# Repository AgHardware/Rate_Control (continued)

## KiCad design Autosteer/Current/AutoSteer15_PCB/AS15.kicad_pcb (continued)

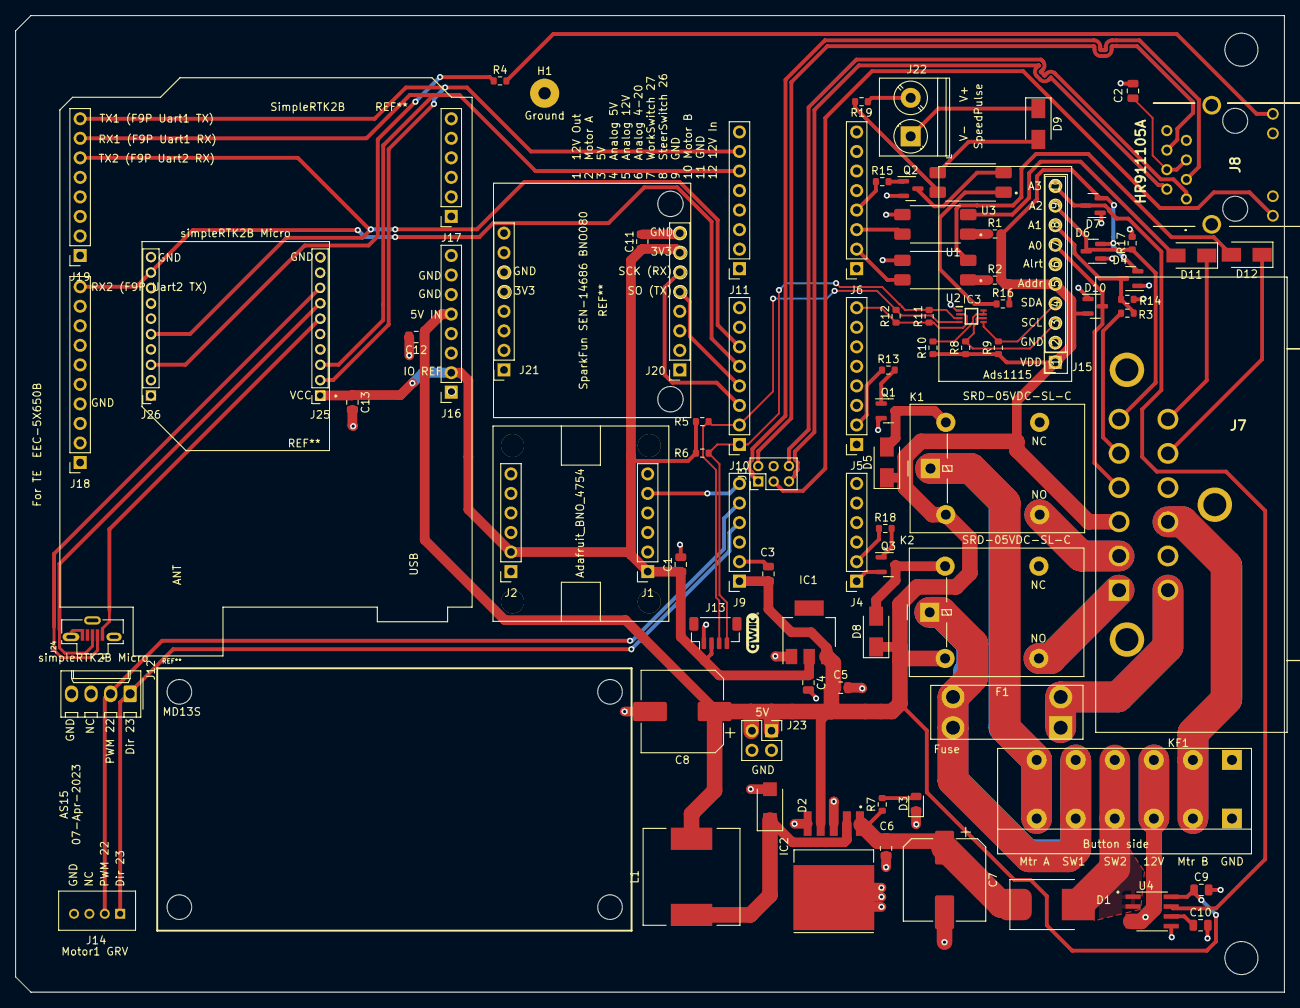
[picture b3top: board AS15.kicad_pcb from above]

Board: 2 copper layers, 165.0 x 127.0 mm, 88 parts (0 on the bottom side), 68 nets.

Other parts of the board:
 : M4; MountingHole_4.3mm_M4
 #2: M4; MountingHole_4.3mm_M4

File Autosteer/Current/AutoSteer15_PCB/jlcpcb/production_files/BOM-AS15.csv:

Comment,Designator,Footprint,LCSC
ACS712ELCTR30AT,U4,SOIC127P600X175-8N,C10681
250,R17,R_0603_1608Metric,C114613
SS36,D2,SMA(DO-214AC),C116712
HR911105A,J8,HR911105A,C12074
150,R4,R_0603_1608Metric,C126805
I2C-3V3,J13,Qwic_vertical,C145961
10uF,C5,C_0805_2012Metric,C15850
S10MC,D1,D_SMC_larger_pads,C169472
1K,"R13,R15,R18,R7",R_0603_1608Metric,C21190
217,"R11,R12",R_0603_1608Metric,C22953
470,"R1,R16,R19,R2",R_0603_1608Metric,C23179
BAV99,"D10,D4,D6,D7",SOT-23,C2500
200K,R10,R_0603_1608Metric,C25811
Conn_01x08_Female,"J10,J11,J16,J19,J20,J21,J5,J6",PinSocket_1x08_P2.54mm_Vertical,C27438
5K,R3,R_0603_1608Metric,C2828621
1uF,C6,C_0805_2012Metric,C28323
ADS1115 - 1001001,"J15,J18",PinSocket_1x10_P2.54mm_Vertical,C2897373
C2935469,F1,Fuse_Holder_C2935469,C2935469
PCA9306DCUR,IC3,PCA9306DCUR,C33196
341,"R8,R9",R_0603_1608Metric,C334802
470uF,C7,CP_Elec_10x10.5,C3350
Conn_01x10_Female,"J25,J26",PinSocket_1x10_P2.00mm_Vertical,C350282
SRD-05VDC-SL-C,"K1,K2",Songle_SRD-05VDC-SL-C,C35449
Motor1 GRV,J14,Grove,C403774
Conn_01x06_Female,"J1,J17,J2,J4,J9",PinSocket_1x06_P2.54mm_Vertical,C40877
2.2K,"R5,R6",R_0603_1608Metric,C4190
3K,R14,R_0603_1608Metric,C4211
SpeedPulse,J22,"TerminalBlock_Phoenix_PT-1,5-2-5.0-H_1x02_P5.00mm_Horizontal",C430621
22uF,C4,C_0805_2012Metric,C45783
KF142V-5.0-6P,KF1,KF142V-5.08-6P,C475138
0.1uF,"C1,C10,C11,C12,C13,C2,C3,C9",C_0805_2012Metric,C49678
BC847,"Q1,Q2,Q3",SOT-23,C57668
105133-0011,J24,MOLEX_105133-0011,C586226
PC817,"U1,U2,U3",SOIC254P960X420-4N,C66405
330uF,C8,CP_Elec_10x10.5,C72510
XL2596,IC2,TO263-5L,C74190
LED,D3,LED_0805_2012Metric,C84256
Motor1,J12,Molex_KK-254_AE-6410-04A_1x04_P2.54mm_Vertical,C86504
Conn_02x02_Counter_Clockwise,J23,PinSocket_2x02_P2.54mm_Vertical,C92273
AZ1117,IC1,SOT-223,C92517
SMDRI127-330MT,L1,TMPA1265SP-101MN-D,C9400
MDD M7,"D11,D12,D5,D8,D9",D_SMA,C95872
DT13-12PA,J7,DT1312PA,
Teensy_Ethernet,J3,PinHeader_2x03_P2.00mm_Vertical,
Ground,H1,MountingHole_2.2mm_M2_DIN965_Pad,

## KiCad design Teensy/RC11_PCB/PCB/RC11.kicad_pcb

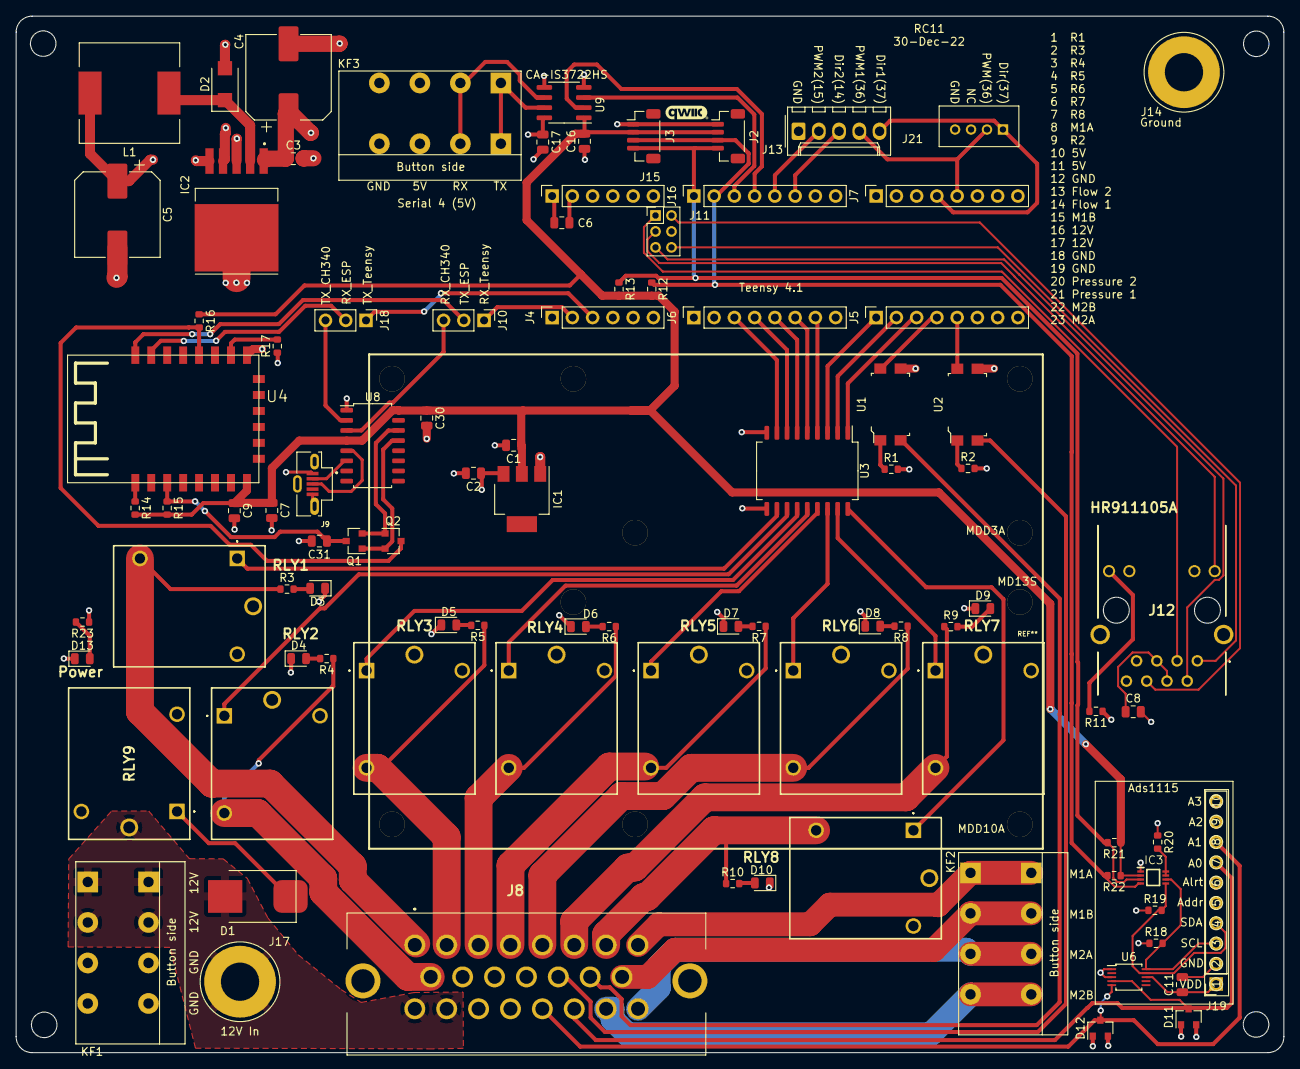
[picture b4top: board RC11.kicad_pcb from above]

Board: 4 copper layers, 159.0 x 130.0 mm, 98 parts (0 on the bottom side), 86 nets.

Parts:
 : MountingHole_3.2mm_M3
 #2,  #3,  #4: MountingHole_3.2mm_M3
C1: 22uF; C_0805_2012Metric
C2, C7: 10uF; C_0805_2012Metric
C3, C31: 1uF; C_0805_2012Metric
C4: 470uF; CP_Elec_10x10.5
C5: 330uF; CP_Elec_10x10.5
C6, C8, C9, C11, C16, C17, C30: 0.1uF; C_0805_2012Metric
D1: S10MC; D_SMC_larger_pads
D2: SS36; SMA(DO-214AC)
D3, D4, D5, D6, D7, D8, D9, D10, D13: LED; LED_0805_2012Metric
D11, D12: BAV99; SOT-23
IC1: AZ1117; SOT-223
IC2: XL2596; TO263-5L
IC3: PCA9306DCUR
J2, J3: I2C-3V3; Qwic_vertical
J4, J15: Conn_01x06_Female; PinSocket_1x06_P2.54mm_Vertical
J5, J6, J7, J16: Conn_01x08_Female; PinSocket_1x08_P2.54mm_Vertical
J8: 776087-1; 7760871
J9: 105133-0011; MOLEX_105133-0011
J10, J18: Conn_01x03_Male; PinHeader_1x03_P2.54mm_Vertical
J11: Teensy_Ethernet; PinHeader_2x03_P2.00mm_Vertical
J12: HR911105A
J13: Conn_01x05; Molex_KK-254_AE-6410-05A_1x05_P2.54mm_Vertical
J14: Ground; PowerPin
J17: 12V In; PowerPin
J19: ADS1115 - 1001001; PinSocket_1x10_P2.54mm_Vertical
J21: Motor1 GRV; Grove
KF1, KF2: KF142V-5.0-4P; KF142V-5.08-4P
KF3: Serial 4 (5V); KF142V-5.08-4P
L1: SMDRI127-330MT; TMPA1265SP-101MN-D
Q1, Q2: BSS138; SOT-23
R1, R2: 200; R_0603_1608Metric
R3, R4, R5, R6, R7, R8, R9, R10, R23: 500; R_0603_1608Metric
R11: 150; R_0603_1608Metric
R12, R13: 2.2K; R_0603_1608Metric
R14, R15, R16, R17: 10K; R_0603_1608Metric
R18, R19: 341; R_0603_1608Metric
R20: 200K; R_0603_1608Metric
R21, R22: 217; R_0603_1608Metric
RLY1, RLY2, RLY3, RLY4, RLY5, RLY6, RLY7, RLY8, RLY9: HF3FF_012-1HST_257_; HF3FF0121HST257
U1, U2: PC817; SMD-4_4.6x7.62mm_P2.54mm
U3: ULN2803A; SOP-18_7x12.5mm_P1.27mm
U4: ESP-12F
U6: ADS1115IDGS - 1001000; TSSOP-10_3x3mm_P0.5mm
U8: CH340C; SOP-16_4.55x10.3mm_P1.27mm
U9: CA-IS3722HS; SOIC-8_3.9x4.9mm_P1.27mm

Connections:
12V_In: D1.2, J8.16, J8.17, J17.1, KF1.1, KF1.2, RLY9.2
+3V3: C1.1, C7.1, C9.1, C16.2, C30.1, IC1.2, IC3.2, J2.2, J3.2, R12.2, R13.2, R14.2, R15.2, R16.1, R21.1, R22.1, U4.8, U8.4, U8.16, U9.1
+5V: C2.1, C5.1, C6.1, C11.1, C17.1, D11.2, D12.2, IC1.3, IC2.4, J8.10, J8.11, J9.1, J15.1, J19.1, J19.5, KF3.3, L1.2, R1.2, R2.2, R11.1, R18.1, R19.1, R20.1, U6.8, U9.8
+12V: C3.1, C4.1, IC2.1, R23.1, RLY1.2, RLY1.3, RLY2.2, RLY2.3, RLY3.2, RLY3.3, RLY4.2, RLY4.3, RLY5.2, RLY5.3, RLY6.2, RLY6.3, RLY7.2, RLY7.3, RLY8.2, RLY8.3, RLY9.4, U3.10
AIN0: D11.3, J8.21, J19.7, U6.4
AIN1: D12.3, J8.20, J19.8, U6.5
EN: C31.1, Q1.3, R15.1, U4.3
FlowPin1: J5.4, U1.4
FlowPin2: J5.5, U2.4
GND: C1.2, C2.2, C3.2, C4.2, C5.2, C6.2, C7.2, C8.2, C9.2, C11.2, C16.1, C17.2, C30.2, C31.2, D2.2, D3.1, D4.1, D5.1, D6.1, D7.1, D8.1, D9.1, D10.1, D11.1, D12.1, D13.1, IC1.1, IC2.3, IC2.5, IC2.6, IC3.1, J2.1, J3.1, J4.1, J8.12, J8.18, J8.19, J9.5, J9.S1, J9.S2, J9.S3, J11.4, J12.8, J12.10, J12.11, J12.MH1, J12.MH2, J13.1, J14.1, J15.2, J16.8, J19.2, J21.4, KF1.3, KF1.4, KF3.4, R17.1, RLY9.3, U1.3, U2.3, U3.9, U4.15, U6.1, U6.3, U8.1, U9.4, U9.5
IO0: Q2.3, R16.2, U4.18
IO14: J13.3, J16.6
IO15: J13.2, J16.5
IO36: J7.5, J13.4, J21.2
IO37: J7.4, J13.5, J21.1
unnamed: C8.1, J12.4, J12.5
unnamed: D1.1, RLY9.1
unnamed: D2.1, IC2.2, L1.1
unnamed: D3.2, R3.2
unnamed: D4.2, R4.2
unnamed: D5.2, R5.2
unnamed: D6.2, R6.2
unnamed: D7.2, R7.2
unnamed: D8.2, R8.2
unnamed: D9.2, R9.2
unnamed: D10.2, R10.2
unnamed: D13.2, R23.2
unnamed: IC3.5, J19.4, R19.2, U6.9
unnamed: IC3.6, J19.3, R18.2, U6.10
unnamed: IC3.7, IC3.8, R20.2
unnamed: J8.8, KF2.1
unnamed: J8.15, KF2.2
unnamed: J8.22, KF2.4
unnamed: J8.23, KF2.3
unnamed: J9.2, U8.6
unnamed: J9.3, U8.5
unnamed: J11.1, J12.3
unnamed: J11.2, J12.6
unnamed: J11.3, J12.9
unnamed: J11.5, J12.2
unnamed: J11.6, J12.1
unnamed: J12.12, R11.2
unnamed: KF3.1, U9.7
unnamed: KF3.2, U9.6
unnamed: Q1.1, Q2.2, U8.13
unnamed: Q1.2, Q2.1, U8.14
unnamed: R1.1, U1.1
unnamed: R2.1, U2.1
unnamed: R14.1, U4.1
unnamed: R17.2, U4.16
unnamed: RLY1.1, U3.11
unnamed: RLY2.1, U3.12
unnamed: RLY3.1, U3.13
unnamed: RLY4.1, U3.14
unnamed: RLY5.1, U3.15
unnamed: RLY6.1, U3.16
unnamed: RLY7.1, U3.17
unnamed: RLY8.1, U3.18
R1: J8.1, R3.1, RLY1.4
R2: J8.9, R4.1, RLY2.4
R3: J8.2, R5.1, RLY3.4
R4: J8.3, R6.1, RLY4.4
R5: J8.4, R7.1, RLY5.4
R6: J8.5, R8.1, RLY6.4
R7: J8.6, R9.1, RLY7.4
R8: J8.7, R10.1, RLY8.4
RLY1: J6.3, U3.8
RLY2: J6.4, U3.7
RLY3: J6.5, U3.6
RLY4: J6.6, U3.5
RLY5: J6.7, U3.4
RLY6: J5.1, U3.3
RLY7: J5.2, U3.2
RLY8: J5.3, U3.1
RX4: J16.4, U9.2
RX_CH340: J10.3, U8.3
RX_ESP: J18.2, U4.21
RX_Teensy: J4.2, J10.1
SCL_Teensy: IC3.3, J2.4, J3.4, J16.1, R13.1, R21.2
SDA_Teensy: IC3.4, J2.3, J3.3, J16.2, R12.1, R22.2
Sensor1: J8.14, U1.2
Sensor2: J8.13, U2.2
TX4: J16.3, U9.3
TX_CH340: J18.3, U8.2
TX_ESP: J10.2, U4.22
TX_Teensy: J4.3, J18.1

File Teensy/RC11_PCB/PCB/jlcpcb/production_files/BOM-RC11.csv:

Comment,Designator,Footprint,LCSC
SS36,D2,SMA(DO-214AC),C116712
HR911105A,J12,HR911105A,C12074
10uF,"C2,C7",C_0805_2012Metric,C15850
I2C-3V3,"J2,J3",Qwic_vertical,C160390
S10MC,D1,D_SMC_larger_pads,C169472
150,R11,R_0603_1608Metric,C22808
217,"R21,R22",R_0603_1608Metric,C22962
341,"R18,R19",R_0603_1608Metric,C23144
500,"R10,R23,R3,R4,R5,R6,R7,R8,R9",R_0603_1608Metric,C23193
BAV99,"D11,D12",SOT-23,C2500
BSS138,"Q1,Q2",SOT-23,C255592
10K,"R14,R15,R16,R17",R_0603_1608Metric,C25804
200K,R20,R_0603_1608Metric,C25811
Conn_01x08_Female,"J16,J5,J6,J7",PinSocket_1x08_P2.54mm_Vertical,C27438
1uF,"C3,C31",C_0805_2012Metric,C28323
ADS1115 - 1001001,J19,PinSocket_1x10_P2.54mm_Vertical,C2897373
HF3FF_012-1HST_257_,"RLY1,RLY2,RLY3,RLY4,RLY5,RLY6,RLY7,RLY8,RLY9",HF3FF0121HST257,C329296
PCA9306DCUR,IC3,PCA9306DCUR,C33196
ADS1115IDGS - 1001000,U6,TSSOP-10_3x3mm_P0.5mm,C37593
776087-1,J8,7760871,C378893
Motor1 GRV,J21,Grove,C403774
Conn_01x06_Female,"J15,J4",PinSocket_1x06_P2.54mm_Vertical,C40877
2.2K,"R12,R13",R_0603_1608Metric,C4190
CA-IS3722HS,U9,SOIC-8_3.9x4.9mm_P1.27mm,C428879
KF142V-5.0-4P,"KF1,KF2,KF3",KF142V-5.08-4P,C475136
Conn_01x03_Male,"J10,J18",PinHeader_1x03_P2.54mm_Vertical,C49257
0.1uF,"C11,C16,C17,C30,C6,C8,C9",C_0805_2012Metric,C49678
105133-0011,J9,MOLEX_105133-0011,C586226
22uF,C1,C_0805_2012Metric,C602037
PC817,"U1,U2",SMD-4_4.6x7.62mm_P2.54mm,C66405
Teensy_Ethernet,J11,PinHeader_2x03_P2.00mm_Vertical,C6694888
330uF,C5,CP_Elec_10x10.5,C72510
470uF,C4,CP_Elec_10x10.5,C72519
XL2596,IC2,TO263-5L,C74190
200,"R1,R2",R_0603_1608Metric,C8218
ESP-12F,U4,ESP-12F,C82891
LED,"D10,D13,D3,D4,D5,D6,D7,D8,D9",LED_0805_2012Metric,C84256
ULN2803A,U3,SOP-18_7x12.5mm_P1.27mm,C845537
CH340C,U8,SOP-16_4.55x10.3mm_P1.27mm,C84681
Conn_01x05,J13,Molex_KK-254_AE-6410-05A_1x05_P2.54mm_Vertical,C86505
AZ1117,IC1,SOT-223,C92517
SMDRI127-330MT,L1,TMPA1265SP-101MN-D,C9400
Ground,J14,PowerPin,
12V In,J17,PowerPin,

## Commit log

2024-01-25 add files
2024-01-25 remove file
2024-01-26 Notes for diode D2
2024-02-05 add ESP32 rate board
2024-02-14 add RC11 enclosure
2024-02-17 fix RC11 board image
2024-04-04 update RC15 installation instructions
2024-05-18 add RC12-2
2024-05-20 update fab components
